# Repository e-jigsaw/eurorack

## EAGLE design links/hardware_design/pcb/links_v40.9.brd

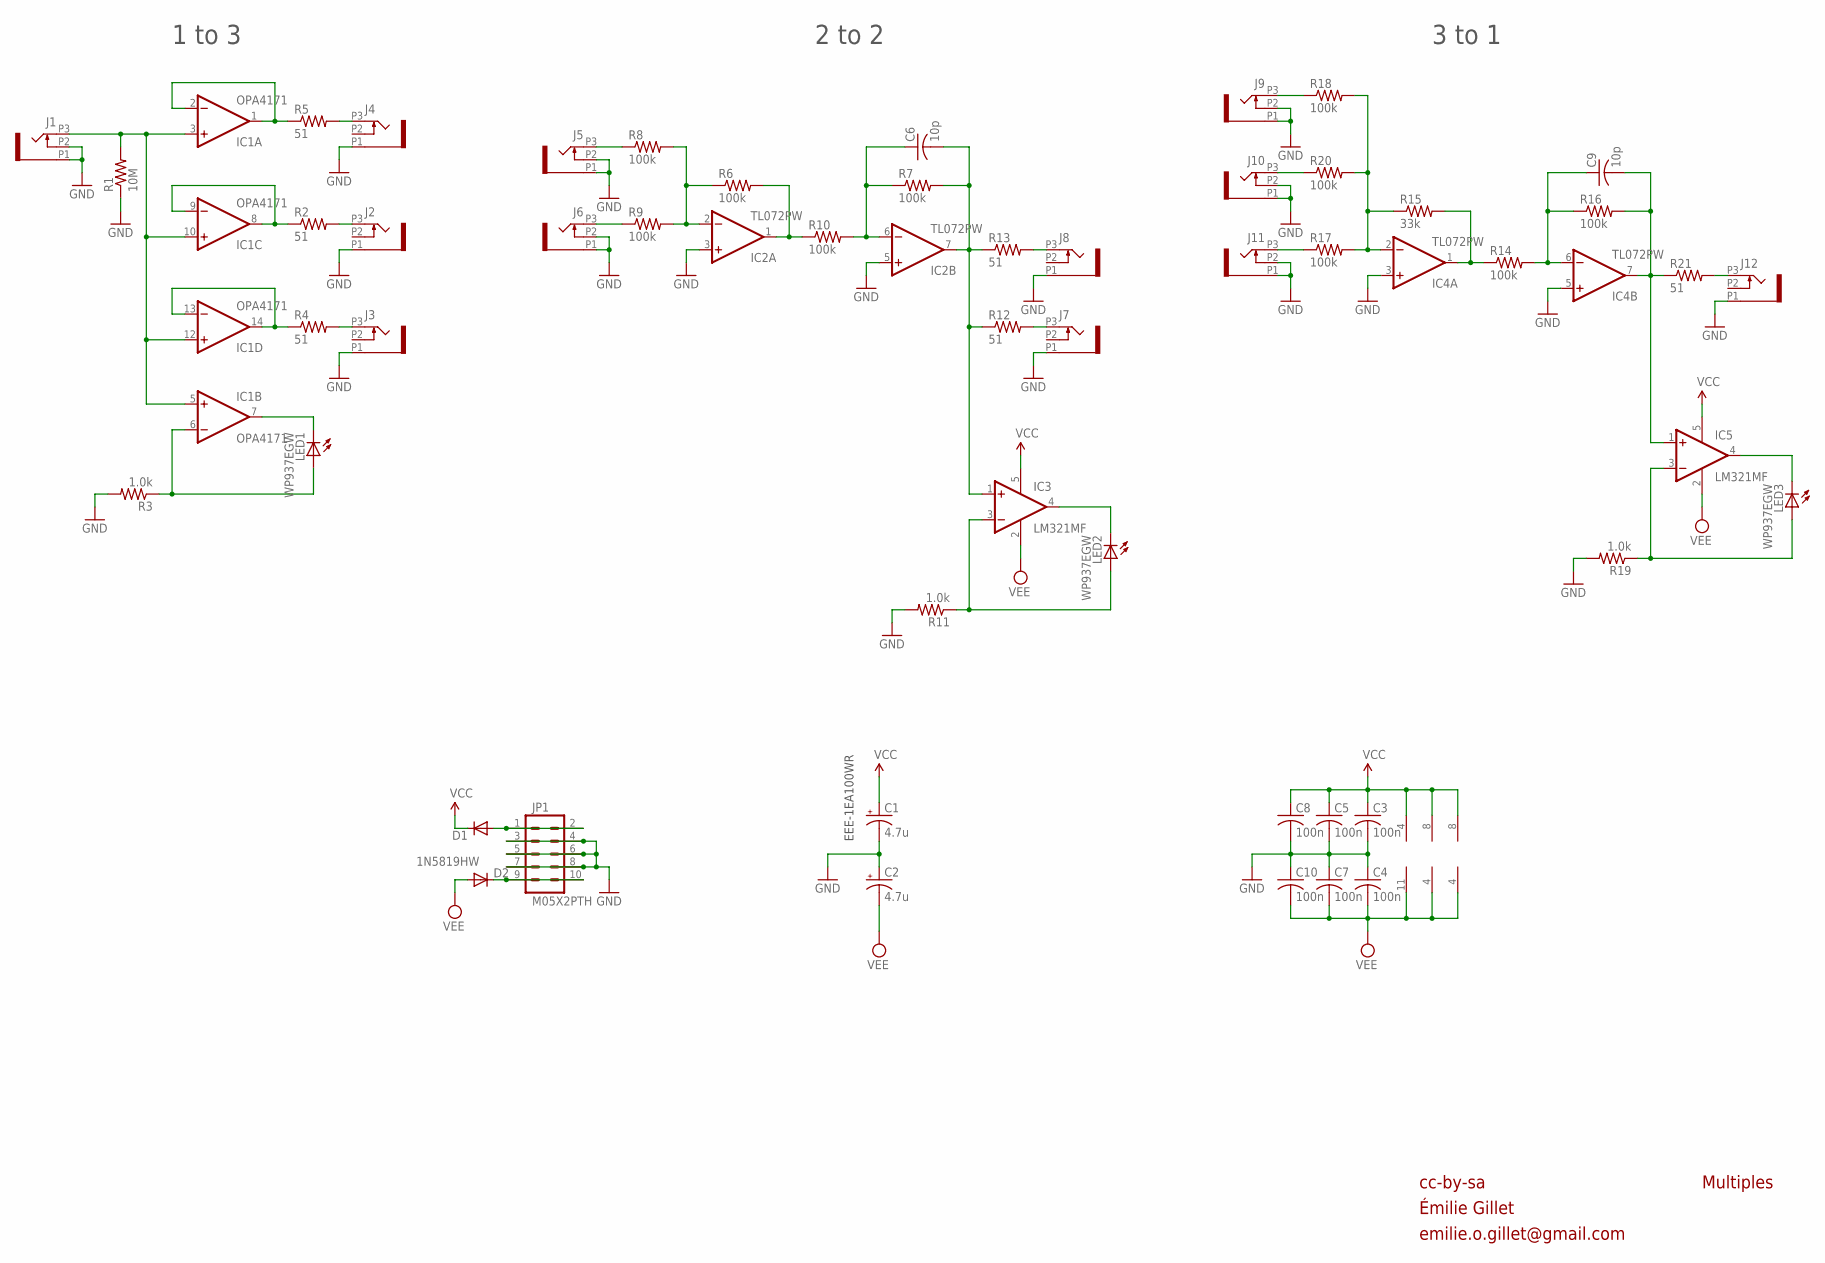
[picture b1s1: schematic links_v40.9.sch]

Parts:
C1, C2: 4.7u; PANASONIC_A
C3, C4, C5, C7, C8, C10: 100n; C0603
C6, C9: 10p; C0603
D1, D2: 1N5819HW; SOD123
IC1: OPA4171; TSSOP14
IC2, IC4: TL072PW; TSSOP8
IC3, IC5: LM321MF; SOT23-5
J1, J2, J3, J4, J5, J6, J7, J8, J9, J10, J11, J12: PJ301_THONKICONN6; WQP_PJ_301M6
JP1: M05X2PTH; AVR_ICSP
LED1, LED2, LED3: WP937EGW; LED3MM
R1: 10M; R0603
R2, R4, R5, R12, R13, R21: 51; R0603
R3, R11, R19: 1.0k; R0603
R6, R7, R8, R9, R10, R14, R16, R17, R18, R20: 100k; R0603
R15: 33k; R0603

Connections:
GND: C1.-, C2.+, C3.2, C4.1, C5.2, C7.1, C8.2, C10.1, IC2.3 (+IN), IC2.5 (+IN), IC4.3 (+IN), IC4.5 (+IN), J1.P1 (1), J1.P2 (2), J2.P1 (1), J3.P1 (1), J4.P1 (1), J5.P1 (1), J5.P2 (2), J6.P1 (1), J6.P2 (2), J7.P1 (1), J8.P1 (1), J9.P1 (1), J9.P2 (2), J10.P1 (1), J10.P2 (2), J11.P1 (1), J11.P2 (2), J12.P1 (1), JP1.3, JP1.4, JP1.5, JP1.6, JP1.7, JP1.8, R1.1, R3.2, R11.2, R19.2
unnamed: IC2.1 (OUT), R6.2, R10.1
unnamed: J11.P3 (3), R17.1
unnamed: IC1.1 (OUT), IC1.2 (-IN), R5.1
unnamed: IC1.8 (OUT), IC1.9 (-IN), R2.1
unnamed: IC1.13 (-IN), IC1.14 (OUT), R4.1
unnamed: D1.A, JP1.1, JP1.2
unnamed: IC1.3 (+IN), IC1.5 (+IN), IC1.10 (+IN), IC1.12 (+IN), J1.P3 (3), R1.2
unnamed: IC1.7 (OUT), LED1.K (C)
unnamed: J10.P3 (3), R20.1
unnamed: J6.P3 (3), R9.1
unnamed: J4.P3 (3), R5.2
unnamed: J2.P3 (3), R2.2
unnamed: J3.P3 (3), R4.2
unnamed: IC3.4 (OUT), LED2.K (C)
unnamed: J5.P3 (3), R8.1
unnamed: J7.P3 (3), R12.2
unnamed: J8.P3 (3), R13.2
unnamed: C9.2, IC4.7 (OUT), IC5.1 (+IN), R16.2, R21.1
unnamed: IC5.3 (-IN), LED3.A, R19.1
unnamed: D2.C, JP1.9, JP1.10
unnamed: IC1.6 (-IN), LED1.A, R3.1
unnamed: J9.P3 (3), R18.1
unnamed: J12.P3 (3), R21.2
unnamed: IC4.2 (-IN), R15.1, R17.2, R18.2, R20.2
unnamed: IC4.1 (OUT), R14.1, R15.2
unnamed: C6.2, IC2.7 (OUT), IC3.1 (+IN), R7.2, R12.1, R13.1
unnamed: C9.1, IC4.6 (-IN), R14.2, R16.1
unnamed: IC3.3 (-IN), LED2.A, R11.1
unnamed: IC5.4 (OUT), LED3.K (C)
unnamed: IC2.2 (-IN), R6.1, R8.2, R9.2
unnamed: C6.1, IC2.6 (-IN), R7.1, R10.2
VCC: C1.+, C3.1, C5.1, C8.1, D1.C, IC1.4 (V+), IC2.8 (V+), IC3.5 (V+), IC4.8 (V+), IC5.5 (V+)
VEE: C2.-, C4.2, C7.2, C10.2, D2.A, IC1.11 (V-), IC2.4 (V-), IC3.2 (V-), IC4.4 (V-), IC5.2 (V-)

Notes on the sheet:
cc-by-sa
Multiples
1 to 3
2 to 2
3 to 1
EEE-1EA100WR
Émilie Gillet
emilie.o.gillet@gmail.com

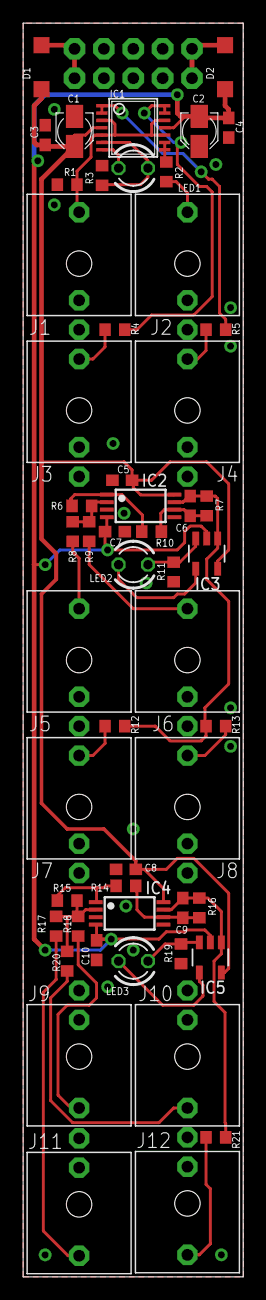
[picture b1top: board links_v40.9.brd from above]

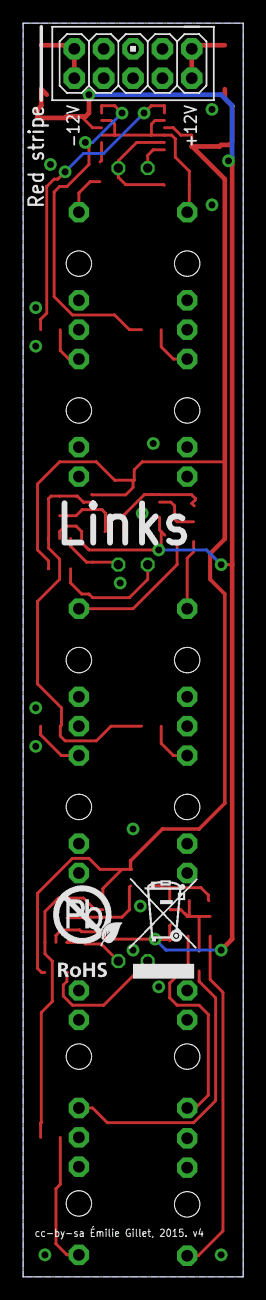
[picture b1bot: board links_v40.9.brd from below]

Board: 2 copper layers, 19.0 x 108.4 mm, 55 parts (2 on the bottom side), 34 nets.

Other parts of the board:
U$2: ROHS

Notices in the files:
links/hardware_design/pcb/links_v40.9.brd:
cc-by-sa Émilie Gillet, 2015. v4
